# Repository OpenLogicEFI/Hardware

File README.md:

# [OpenLogicEFI](https://www.openlogicefi.com)
Formerly: DetonationEMS

</div>

OpenLogicEFI ECU's are based off an open source project called Speeduino by Josh Stewart. Currently all released boards use official Speeduino firmware. In TunerStudio set to "Board Layout" to "Speeduino 0.4"

</div>

# License
All designs are released under the [TAPR Open Hardware License v1.0](https://files.tapr.org/OHL/TAPR_Open_Hardware_License_v1.0.txt)

</div>

# Documentation

- The [Official Speeduino Manual](https://wiki.speeduino.com), documents and discord are the best places to start.

- [Official Speeduino Forum](https://speeduino.com/forum)

- [Official Speeduino Discord](https://discord.gg/jcmar3zfSJ)

- [Additional Documentation and Links](https://www.openlogicefi.com/support)

</div>

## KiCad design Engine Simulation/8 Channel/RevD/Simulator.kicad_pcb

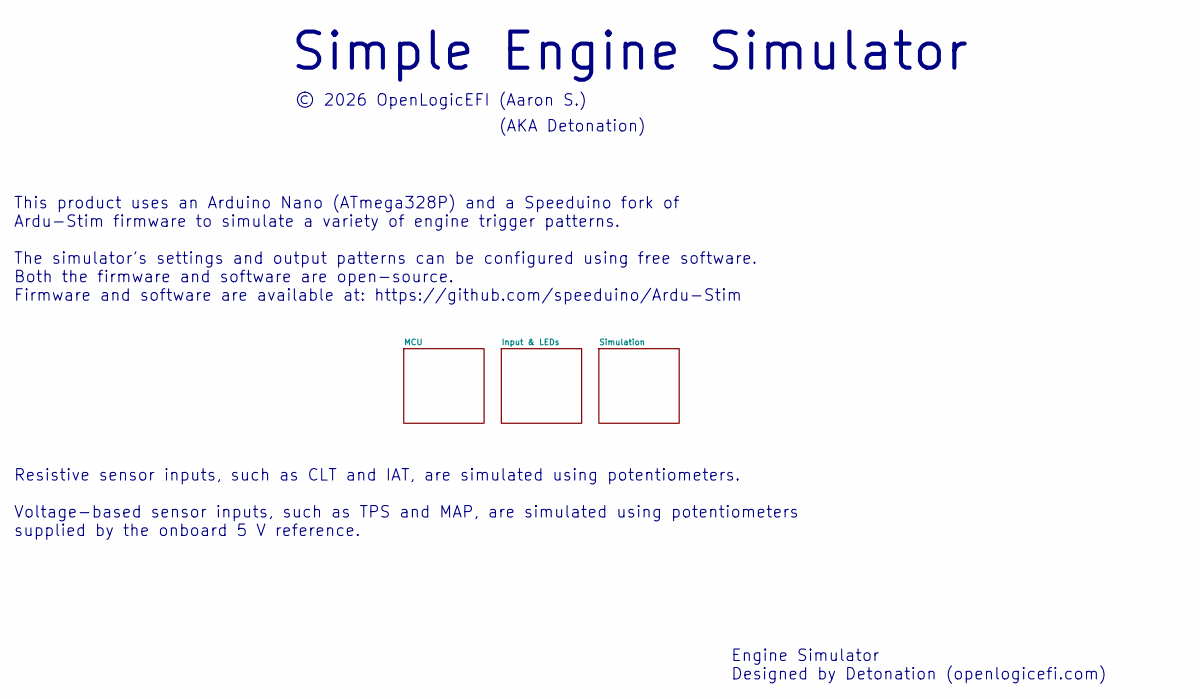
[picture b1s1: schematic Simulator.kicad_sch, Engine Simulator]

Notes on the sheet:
This product uses an Arduino Nano (ATmega328P) and a Speeduino fork of Ardu-Stim firmware to simulate a variety of engine trigger patterns. The simulator's settings and output patterns can be configured using free software. Both the firmware and software are open-source. Firmware and software are a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
Engine Simulator Designed by Detonation (openlogicefi.com)
(AKA Detonation)
Resistive sensor inputs, such as CLT and IAT, are simulated using potentiometers. Voltage-based sensor inputs, such as TPS and MAP, are simulated using potentiometers supplied by the onboard 5 V reference.
© 2026 OpenLogicEFI (Aaron S.)
Simple Engine Simulator

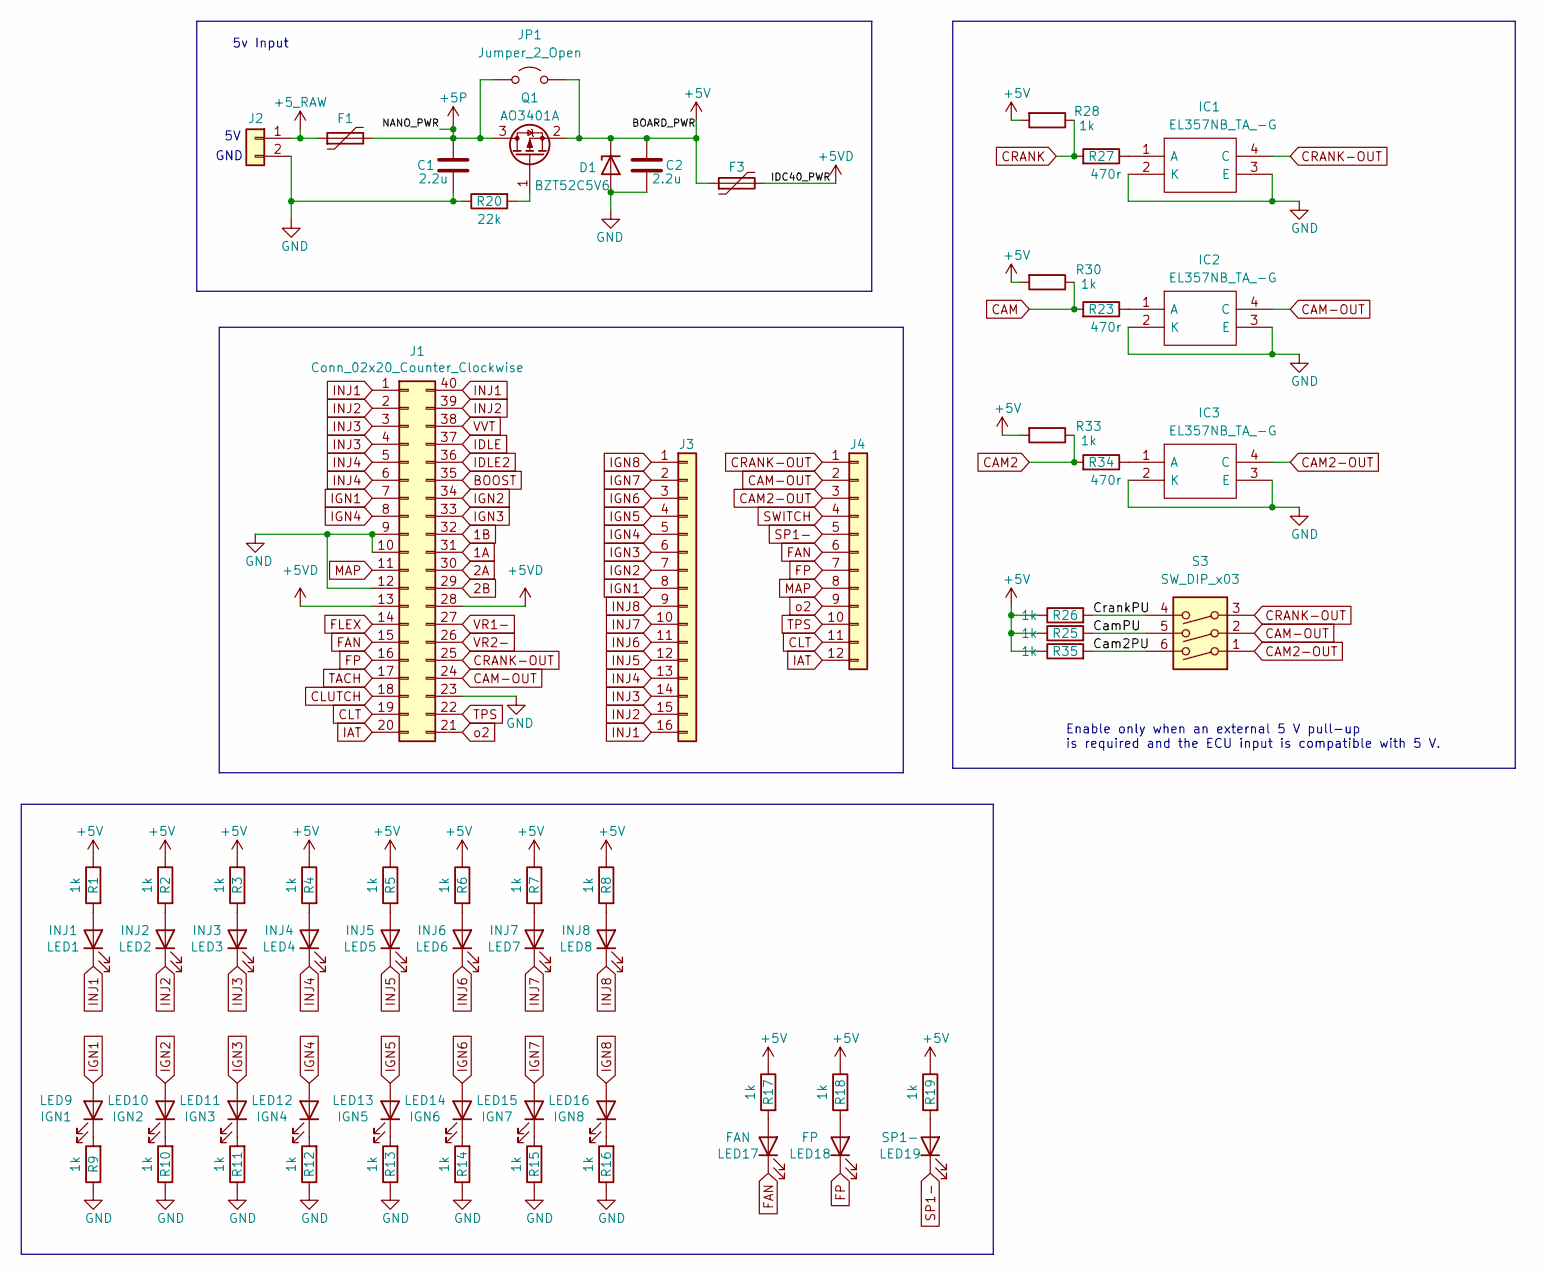
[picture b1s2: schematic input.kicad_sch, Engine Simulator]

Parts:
C1, C2: 2.2u; C_1206_3216Metric; LCSC C50254
D1: BZT52C5V6; D_SOD-123; LCSC C19077402
F1, F3: 1206L100/24NR; Fuse_1206_3216Metric; LCSC C7542957
IC1, IC2, IC3: EL357NB_TA_-G; SOP-4_3.8x4.1mm_P2.54mm; Manufacturer_Part_Number EL357NB(TA)-G; Mouser Part Number 638-EL357NBTAG
J1: Conn_02x20_Counter_Clockwise; IDC-Header_2x20_P2.54mm_Vertical_Speeduino
J2: Conn_01x04; TerminalBlock_Phoenix_PT-1,5-2-5.0-H_1x02_P5.00mm_Horizontal
J3: Conn_01x08; TerminalBlock_Phoenix_PT-1,5-16-3.5-H_1x16_P3.50mm_Horizont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
J4: Conn_01x10; TerminalBlock_Phoenix_PT-1,5-12-3.5-H_1x12_P3.50mm_Horizont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
JP1: Jumper_2_Open; SolderJumper-2_P1.3mm_Open_Rounded_NOCOURTYARD
LED1: INJ1; LED_0603_1608Metric; LCSC C2286
LED2: INJ2; LED_0603_1608Metric; LCSC C2286
LED3: INJ3; LED_0603_1608Metric; LCSC C2286
LED4: INJ4; LED_0603_1608Metric; LCSC C2286
LED5: INJ5; LED_0603_1608Metric; LCSC C2286
LED6: INJ6; LED_0603_1608Metric; LCSC C2286
LED7: INJ7; LED_0603_1608Metric; LCSC C2286
LED8: INJ8; LED_0603_1608Metric; LCSC C2286
LED9: IGN1; LED_0603_1608Metric; LCSC C2286
LED10: IGN2; LED_0603_1608Metric; LCSC C2286
LED11: IGN3; LED_0603_1608Metric; LCSC C2286
LED12: IGN4; LED_0603_1608Metric; LCSC C2286
LED13: IGN5; LED_0603_1608Metric; LCSC C2286
LED14: IGN6; LED_0603_1608Metric; LCSC C2286
LED15: IGN7; LED_0603_1608Metric; LCSC C2286
LED16: IGN8; LED_0603_1608Metric; LCSC C2286
LED17: FAN; LED_0603_1608Metric; LCSC C2286
LED18: FP; LED_0603_1608Metric; LCSC C2286
LED19: SP1-; LED_0603_1608Metric; LCSC C2286
Q1: AO3401A; SOT-23
R1, R2, R3, R4, R5, R6, R7, R8, R9, R10, R11, R12, R13, R14, R15, R16, R17, R18, R19, R25, R26, R28, R30, R33, R35: 1k; R_0603_1608Metric; LCSC C21190
R20: 22k; R_0805_2012Metric; LCSC C17560
R23, R27, R34: 470r; R_0603_1608Metric; LCSC C23179
S3: SW_DIP_x03; SW_DIP_SPSTx03_Slide_9.78x9.8mm_W7.62mm_P2.54mm

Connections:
1A: J1.31
1B: J1.32
2A: J1.30
2B: J1.29
+5P: C1.1, F1.2, JP1.1 (A), Q1.3 (D); also elsewhere on the board
+5V: C2.1, D1.1 (K), F3.1, JP1.2 (B), Q1.2 (S), R1.1, R2.1, R3.1, R4.1, R5.1, R6.1, R7.1, R8.1, R17.1, R18.1, R19.1, R25.1, R26.1, R28.2, R30.2, R33.2, R35.1; also elsewhere on the board
+5VD: F3.2, J1.13, J1.28
+5_RAW: F1.1, J2.1
/Input & LED's/Cam2PU: R35.2, S3.6
/Input & LED's/CamPU: R25.2, S3.5
/Input & LED's/CrankPU: R26.2, S3.4
BOOST: J1.35
CAM: R23.2, R30.1; also elsewhere on the board
CAM2: R33.1, R34.2; also elsewhere on the board
CAM2-OUT: IC3.4 (C), J4.3, S3.1
CAM-OUT: IC2.4 (C), J1.24, J4.2, S3.2
CLT: J1.19, J4.11; also elsewhere on the board
CLUTCH: J1.18
CRANK: R27.2, R28.1; also elsewhere on the board
CRANK-OUT: IC1.4 (C), J1.25, J4.1, S3.3
FAN: J1.15, J4.6, LED17.1 (K)
FLEX: J1.14
FP: J1.16, J4.7, LED18.1 (K)
GND: C1.2, C2.2, D1.2 (A), IC1.2 (K), IC1.3 (E), IC2.2 (K), IC2.3 (E), IC3.2 (K), IC3.3 (E), J1.9, J1.10, J1.12, J1.23, J2.2, R9.1, R10.1, R11.1, R12.1, R13.1, R14.1, R15.1, R16.1, R20.1; also elsewhere on the board
IAT: J1.20, J4.12; also elsewhere on the board
IDLE: J1.37
IDLE2: J1.36
IGN1: J1.7, J3.8, LED9.2 (A)
IGN2: J1.34, J3.7, LED10.2 (A)
IGN3: J1.33, J3.6, LED11.2 (A)
IGN4: J1.8, J3.5, LED12.2 (A)
IGN5: J3.4, LED13.2 (A)
IGN6: J3.3, LED14.2 (A)
IGN7: J3.2, LED15.2 (A)
IGN8: J3.1, LED16.2 (A)
INJ1: J1.1, J1.40, J3.16, LED1.1 (K)
INJ2: J1.2, J1.39, J3.15, LED2.1 (K)
INJ3: J1.3, J1.4, J3.14, LED3.1 (K)
INJ4: J1.5, J1.6, J3.13, LED4.1 (K)
INJ5: J3.12, LED5.1 (K)
INJ6: J3.11, LED6.1 (K)
INJ7: J3.10, LED7.1 (K)
INJ8: J3.9, LED8.1 (K)
MAP: J1.11, J4.8; also elsewhere on the board
unnamed: IC1.1 (A), R27.1
unnamed: IC2.1 (A), R23.1
unnamed: IC3.1 (A), R34.1
unnamed: LED1.2 (A), R1.2
unnamed: LED2.2 (A), R2.2
unnamed: LED3.2 (A), R3.2
unnamed: LED4.2 (A), R4.2
unnamed: LED5.2 (A), R5.2
unnamed: LED6.2 (A), R6.2
unnamed: LED7.2 (A), R7.2
unnamed: LED8.2 (A), R8.2
unnamed: LED9.1 (K), R9.2
unnamed: LED10.1 (K), R10.2
unnamed: LED11.1 (K), R11.2
unnamed: LED12.1 (K), R12.2
unnamed: LED13.1 (K), R13.2
unnamed: LED14.1 (K), R14.2
unnamed: LED15.1 (K), R15.2
unnamed: LED16.1 (K), R16.2
unnamed: LED17.2 (A), R17.2
unnamed: LED18.2 (A), R18.2
unnamed: LED19.2 (A), R19.2
unnamed: Q1.1 (G), R20.2
SP1-: J4.5, LED19.1 (K)
SWITCH: J4.4; also elsewhere on the board
TACH: J1.17
TPS: J1.22, J4.10; also elsewhere on the board
VR1-: J1.27
VR2-: J1.26
VVT: J1.38
o2: J1.21, J4.9; also elsewhere on the board

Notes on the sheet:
Enable only when an external 5 V pull-up is required and the ECU input is compatible with 5 V.
GND
5v Input

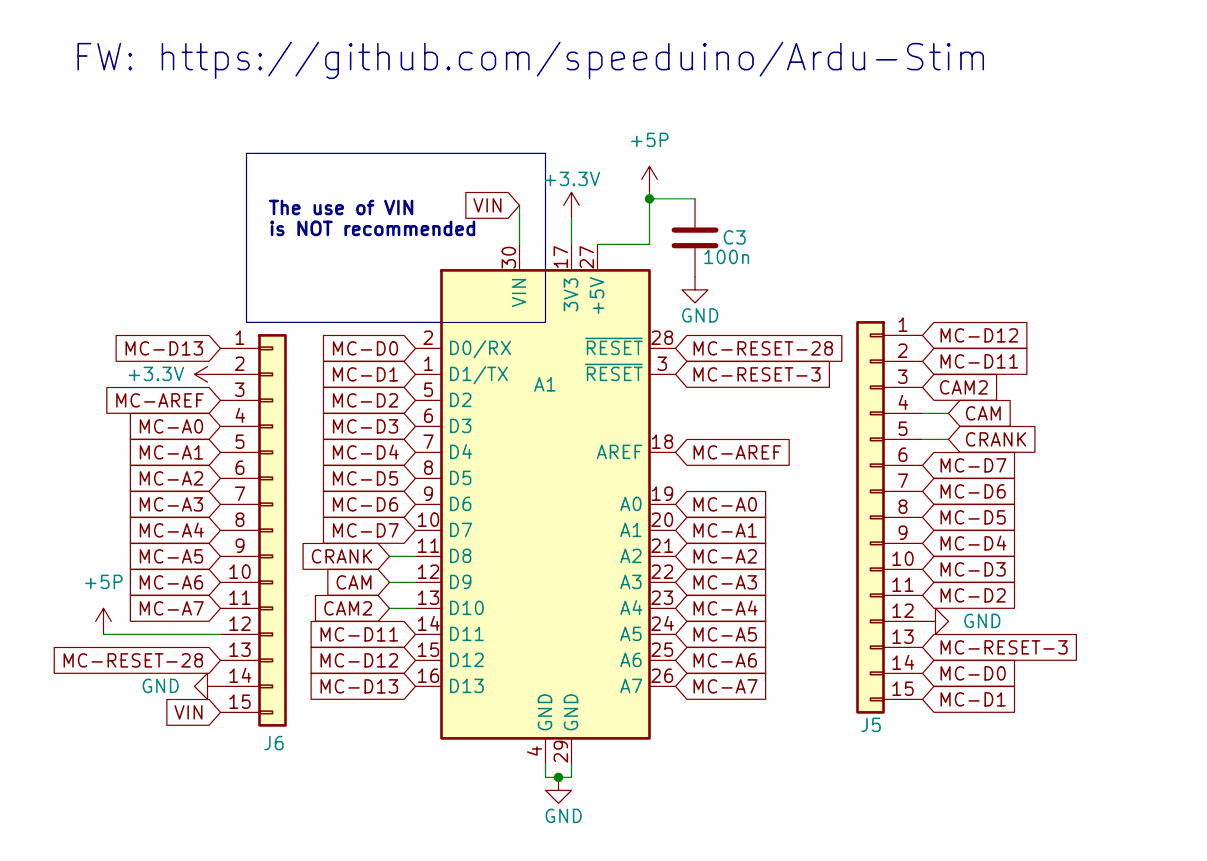
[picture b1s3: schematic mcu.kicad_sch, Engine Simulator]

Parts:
A1: Arduino_Nano_v3.x; Arduino_Nano
C3: 100n; C_0805_2012Metric; LCSC C49678
J5, J6: Conn_01x04; PinSocket_1x15_P2.54mm_Vertical

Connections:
+3.3V: A1.17 (3V3), J6.2
+5P: A1.27 (+5V), C3.1, J6.12; also elsewhere on the board
CAM: A1.12 (D9), J5.4; also elsewhere on the board
CAM2: A1.13 (D10), J5.3; also elsewhere on the board
CRANK: A1.11 (D8), J5.5; also elsewhere on the board
GND: A1.4 (GND), A1.29 (GND), C3.2, J5.12, J6.14; also elsewhere on the board
MC-A0: A1.19 (A0), J6.4; also elsewhere on the board
MC-A1: A1.20 (A1), J6.5
MC-A2: A1.21 (A2), J6.6
MC-A3: A1.22 (A3), J6.7
MC-A4: A1.23 (A4), J6.8
MC-A5: A1.24 (A5), J6.9
MC-A6: A1.25 (A6), J6.10
MC-A7: A1.26 (A7), J6.11
MC-AREF: A1.18 (AREF), J6.3
MC-D0: A1.2 (D0/RX), J5.14
MC-D1: A1.1 (D1/TX), J5.15
MC-D2: A1.5 (D2), J5.11
MC-D3: A1.6 (D3), J5.10
MC-D4: A1.7 (D4), J5.9
MC-D5: A1.8 (D5), J5.8
MC-D6: A1.9 (D6), J5.7
MC-D7: A1.10 (D7), J5.6
MC-D11: A1.14 (D11), J5.2
MC-D12: A1.15 (D12), J5.1
MC-D13: A1.16 (D13), J6.1
MC-RESET-3: A1.3 (~RESET), J5.13
MC-RESET-28: A1.28 (~RESET), J6.13
VIN: A1.30 (VIN), J6.15

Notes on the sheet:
FW: https://github.com/speeduino/Ardu-Stim
The use of VIN is NOT recommended

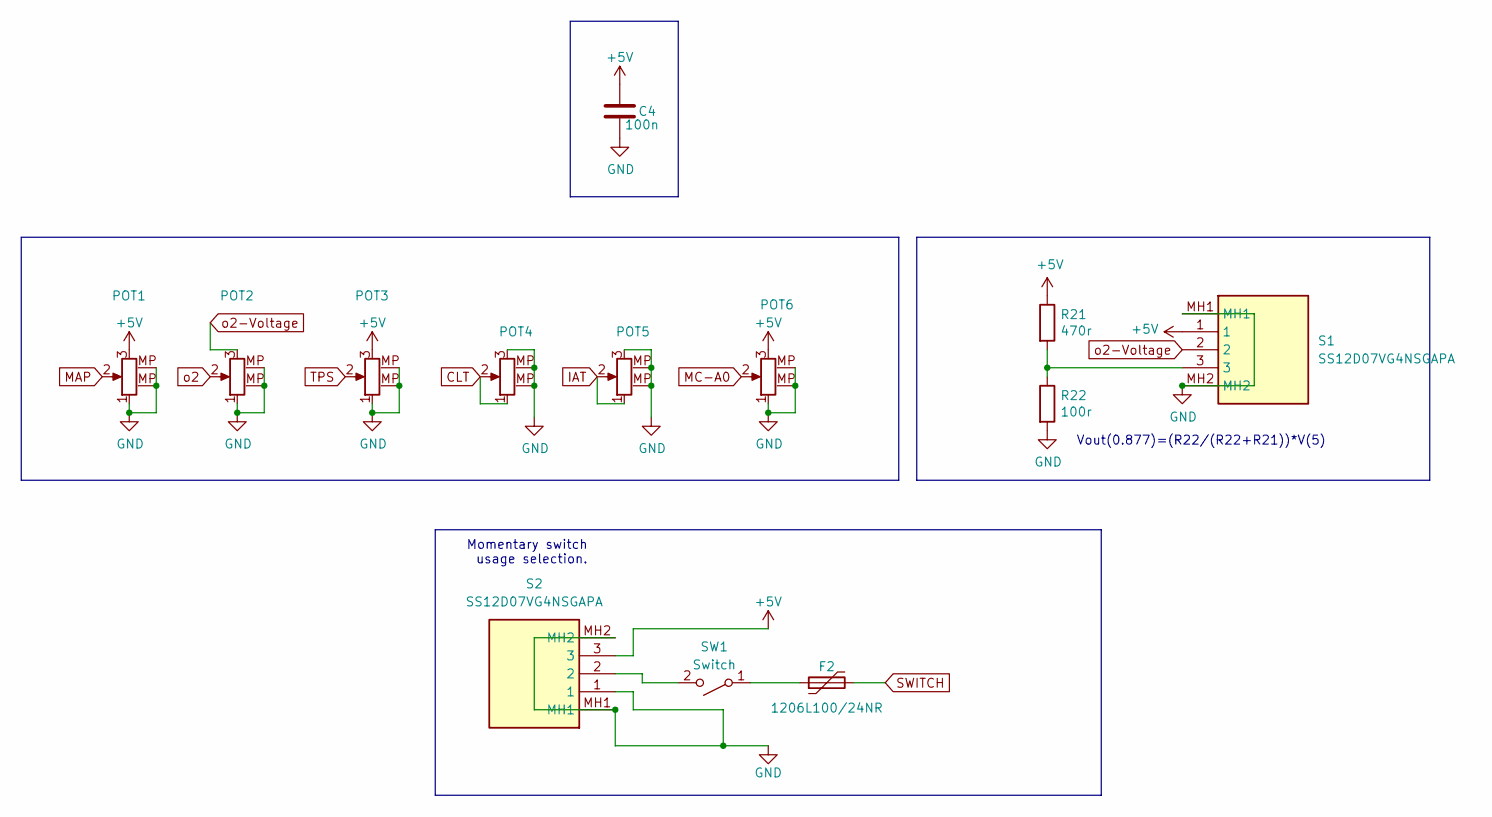
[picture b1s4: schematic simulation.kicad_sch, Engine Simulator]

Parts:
C4: 100n; C_0805_2012Metric; LCSC C49678
F2: 1206L100/24NR; Fuse_1206_3216Metric; LCSC C7542957
POT1: IAT; Potentiometer_Alps_RK09K_Single_Vertical; LCSC C202373
POT2: CLT; Potentiometer_Alps_RK09K_Single_Vertical; LCSC C202373
POT3: MAP/SP1; Potentiometer_Alps_RK09K_Single_Vertical; LCSC C202373
POT4: TPS; Potentiometer_Alps_RK09K_Single_Vertical; LCSC C202373
POT5: o2; Potentiometer_Alps_RK09K_Single_Vertical; LCSC C202373
POT6: RPM; Potentiometer_Alps_RK09K_Single_Vertical; LCSC C202373
R21: 470r; R_0603_1608Metric; LCSC C23179
R22: 100r; R_0603_1608Metric; LCSC C22775
S1, S2: SS12D07VG4NSGAPA; Manufacturer_Part_Number SS12D07VG4NSGAPA; Mouser Part Number N/A
SW1: Switch; SW_PUSH_6mm_H9.5mm

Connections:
+5V: C4.1, POT1.3, POT3.3, POT6.3, R21.1, S1.1, S2.3; also elsewhere on the board
CLT: POT4.1, POT4.2; also elsewhere on the board
GND: C4.2, POT1.1, POT1.MP (Mounting_Tap), POT2.1, POT2.MP (Mounting_Tap), POT3.1, POT3.MP (Mounting_Tap), POT4.3, POT4.MP (Mounting_Tap), POT5.3, POT5.MP (Mounting_Tap), POT6.1, POT6.MP (Mounting_Tap), R22.2, S1.MH1, S1.MH2, S2.1, S2.MH1, S2.MH2; also elsewhere on the board
IAT: POT5.1, POT5.2; also elsewhere on the board
MAP: POT1.2; also elsewhere on the board
MC-A0: POT6.2; also elsewhere on the board
unnamed: R21.2, R22.1, S1.3
unnamed: F2.1, SW1.1 (A)
unnamed: S2.2, SW1.2 (B)
SWITCH: F2.2; also elsewhere on the board
TPS: POT3.2; also elsewhere on the board
o2: POT2.2; also elsewhere on the board
o2-Voltage: POT2.3, S1.2

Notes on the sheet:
Vout(0.877)=(R22/(R22+R21))*V(5)
Momentary switch usage selection.

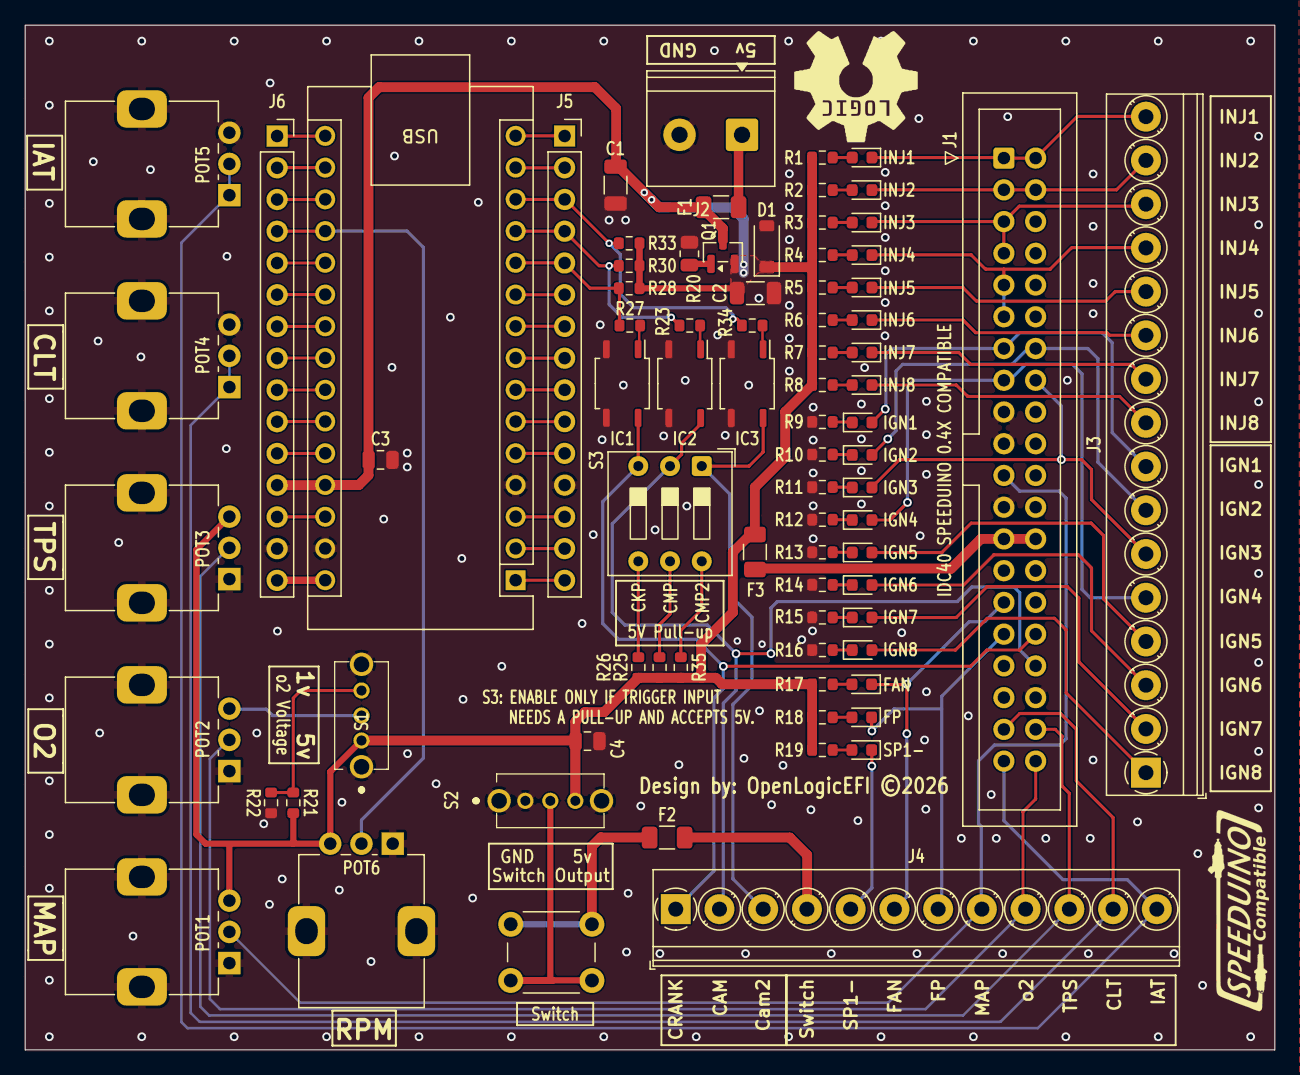
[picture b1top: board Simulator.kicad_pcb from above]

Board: 2 copper layers, 100.0 x 82.0 mm, 81 parts (1 on the bottom side), 90 nets.

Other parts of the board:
G2: Logo_Open_Hardware_Small; SpeeduinoCompatible-17mm

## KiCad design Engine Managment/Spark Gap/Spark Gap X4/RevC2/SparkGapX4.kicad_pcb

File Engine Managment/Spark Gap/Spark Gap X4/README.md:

# Spark Gap

Spark Gap x4 is an open-source, universal standalone engine management system designed
for the budget-minded enthusiast seeking a comprehensive all-in-one solution.
It is compact and feature-rich, utilizing an off-the-shelf case and connector.

Board Selection in tuner studio for this ECU is "Speeduino v0.4"

RevA: Initial Release 2024

RevB: Never released

RevC: Released 2025

RevC2: Released 2026

www.OpenLogicEFI.com

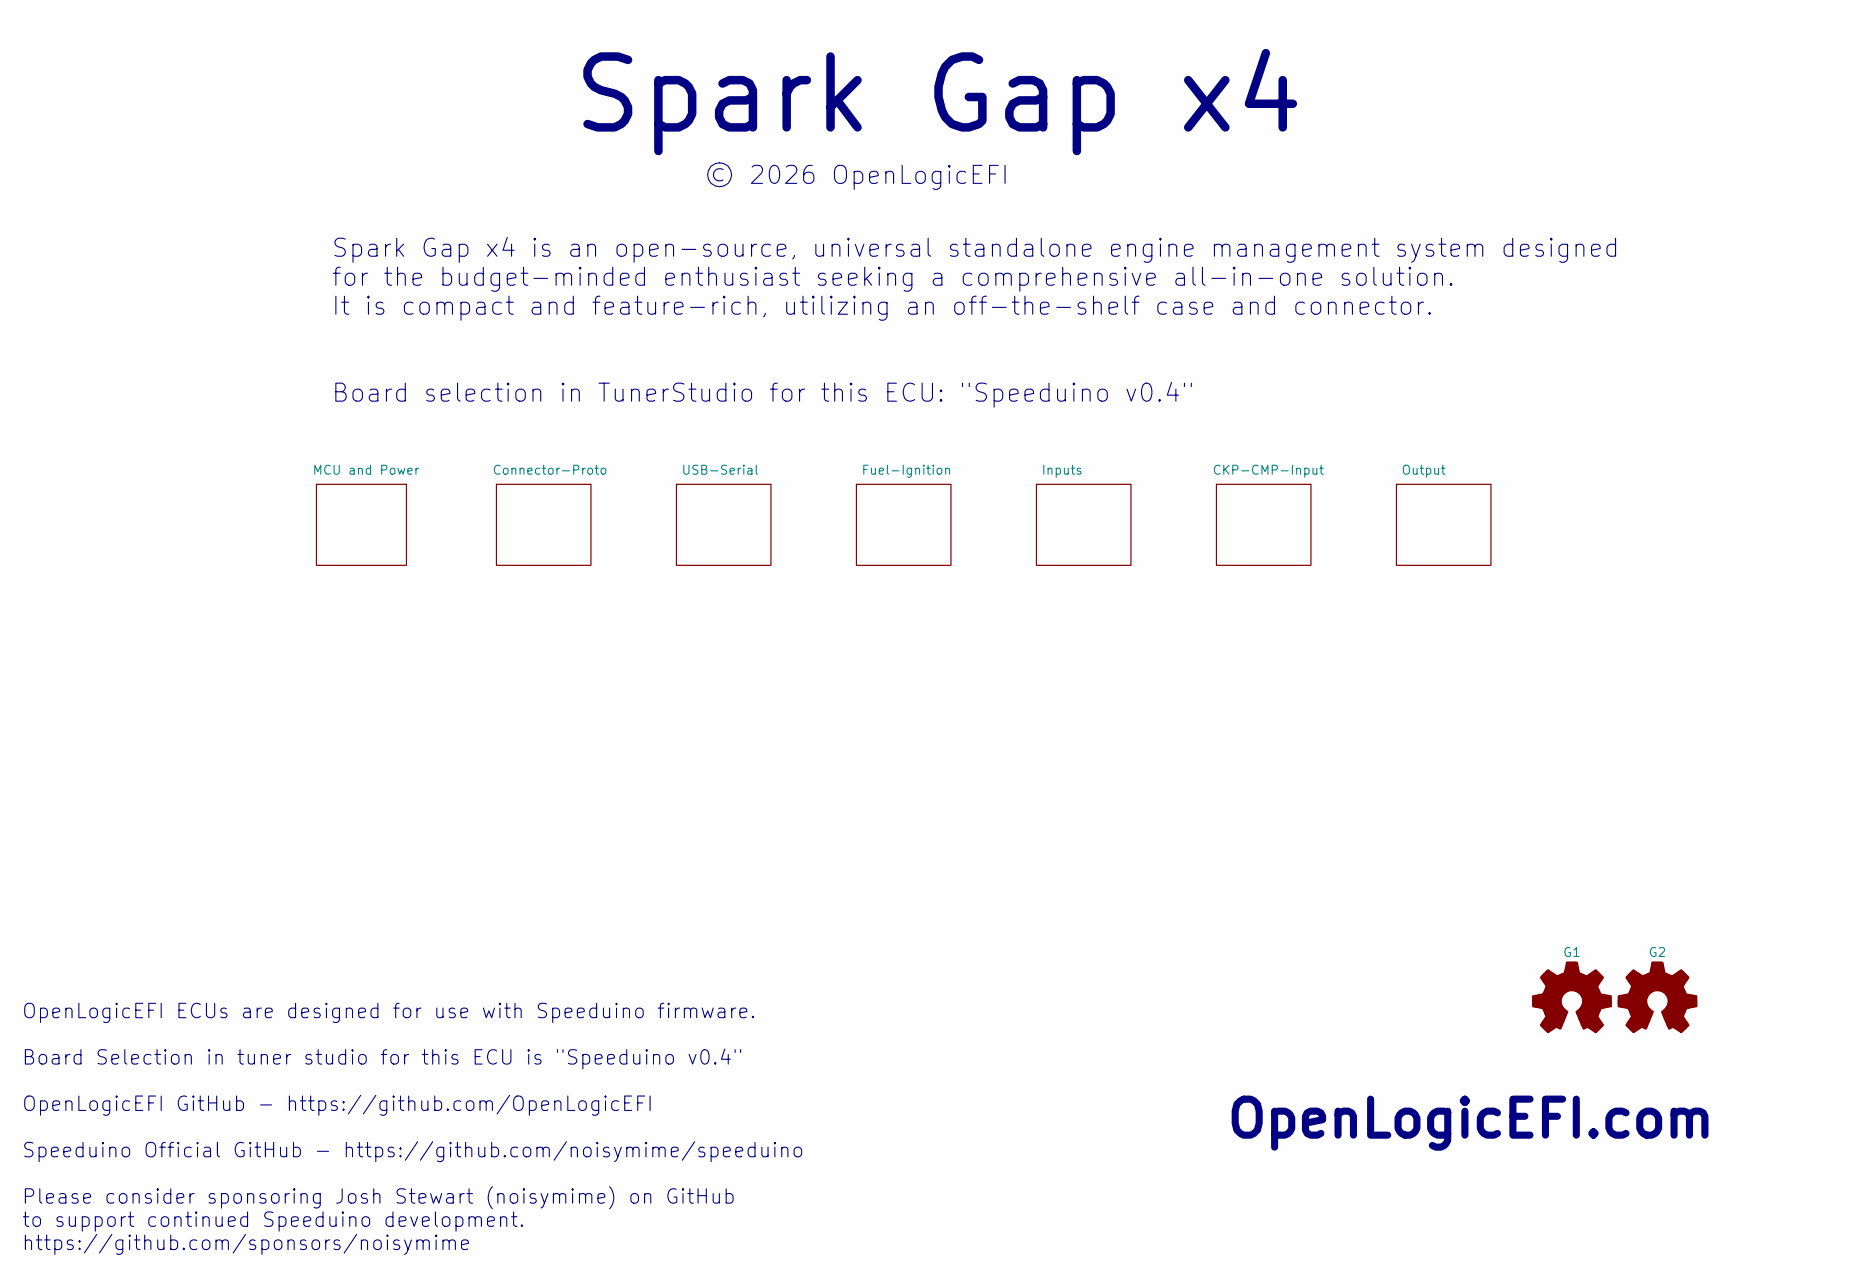
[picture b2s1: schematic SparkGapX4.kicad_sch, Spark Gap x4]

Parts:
G1: Logo_Open_Hardware_Small; SpeeduinoCompatible-14mm
G2: Logo_Open_Hardware_Small; OSHW-Logo2_7.3x6mm_SilkScreen

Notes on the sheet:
OpenLogicEFI ECUs are designed for use with Speeduino firmware. Board Selection in tuner studio for this ECU is "Speeduino v0.4" OpenLogicEFI GitHub - https://github.com/OpenLogicEFI Speeduino Official GitHub - https://github.com/noisymime/speeduino Please consider sponsoring Josh Stewart (noisymim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
© 2026 OpenLogicEFI
OpenLogicEFI.com
Spark Gap x4 is an open-source, universal standalone engine management system designed for the budget-minded enthusiast seeking a comprehensive all-in-one solution. It is compact and feature-rich, utilizing an off-the-shelf case and connector. Board selection in TunerStudio for this ECU: "Speeduino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
Spark Gap x4

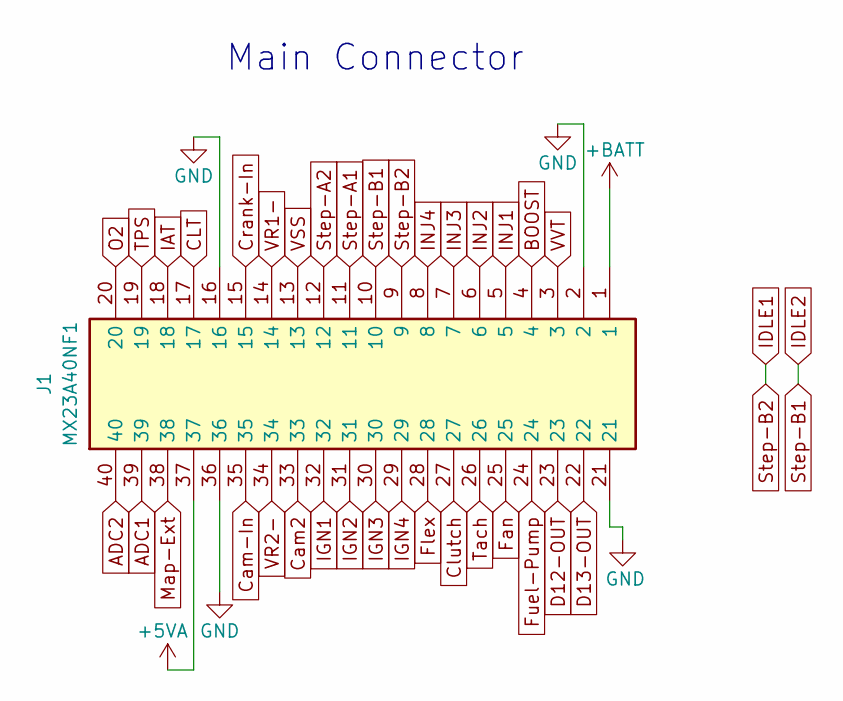
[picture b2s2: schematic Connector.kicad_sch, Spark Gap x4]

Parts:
J1: MX23A40NF1; Manufacture Part Number MX23A40NF1

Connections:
+5V: J1.37; also elsewhere on the board
+BATT: J1.1; also elsewhere on the board
ADC1: J1.39; also elsewhere on the board
ADC2: J1.40; also elsewhere on the board
BOOST: J1.4; also elsewhere on the board
CLT: J1.17; also elsewhere on the board
Cam2: J1.33; also elsewhere on the board
Cam-In: J1.35; also elsewhere on the board
Clutch: J1.27; also elsewhere on the board
Crank-In: J1.15; also elsewhere on the board
D12-OUT: J1.23; also elsewhere on the board
D13-OUT: J1.22; also elsewhere on the board
Fan: J1.25; also elsewhere on the board
Flex: J1.28; also elsewhere on the board
Fuel-Pump: J1.24; also elsewhere on the board
GND: J1.2, J1.16, J1.21, J1.36; also elsewhere on the board
IAT: J1.18; also elsewhere on the board
IDLE1: J1.9; also elsewhere on the board
IDLE2: J1.10; also elsewhere on the board
IGN1: J1.32; also elsewhere on the board
IGN2: J1.31; also elsewhere on the board
IGN3: J1.30; also elsewhere on the board
IGN4: J1.29; also elsewhere on the board
INJ1: J1.5; also elsewhere on the board
INJ2: J1.6; also elsewhere on the board
INJ3: J1.7; also elsewhere on the board
INJ4: J1.8; also elsewhere on the board
Map-Ext: J1.38; also elsewhere on the board
O2: J1.20; also elsewhere on the board
Step-A1: J1.11; also elsewhere on the board
Step-A2: J1.12; also elsewhere on the board
TPS: J1.19; also elsewhere on the board
Tach: J1.26; also elsewhere on the board
VR1-: J1.14; also elsewhere on the board
VR2-: J1.34; also elsewhere on the board
VSS: J1.13; also elsewhere on the board
VVT: J1.3; also elsewhere on the board

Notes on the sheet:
Main Connector

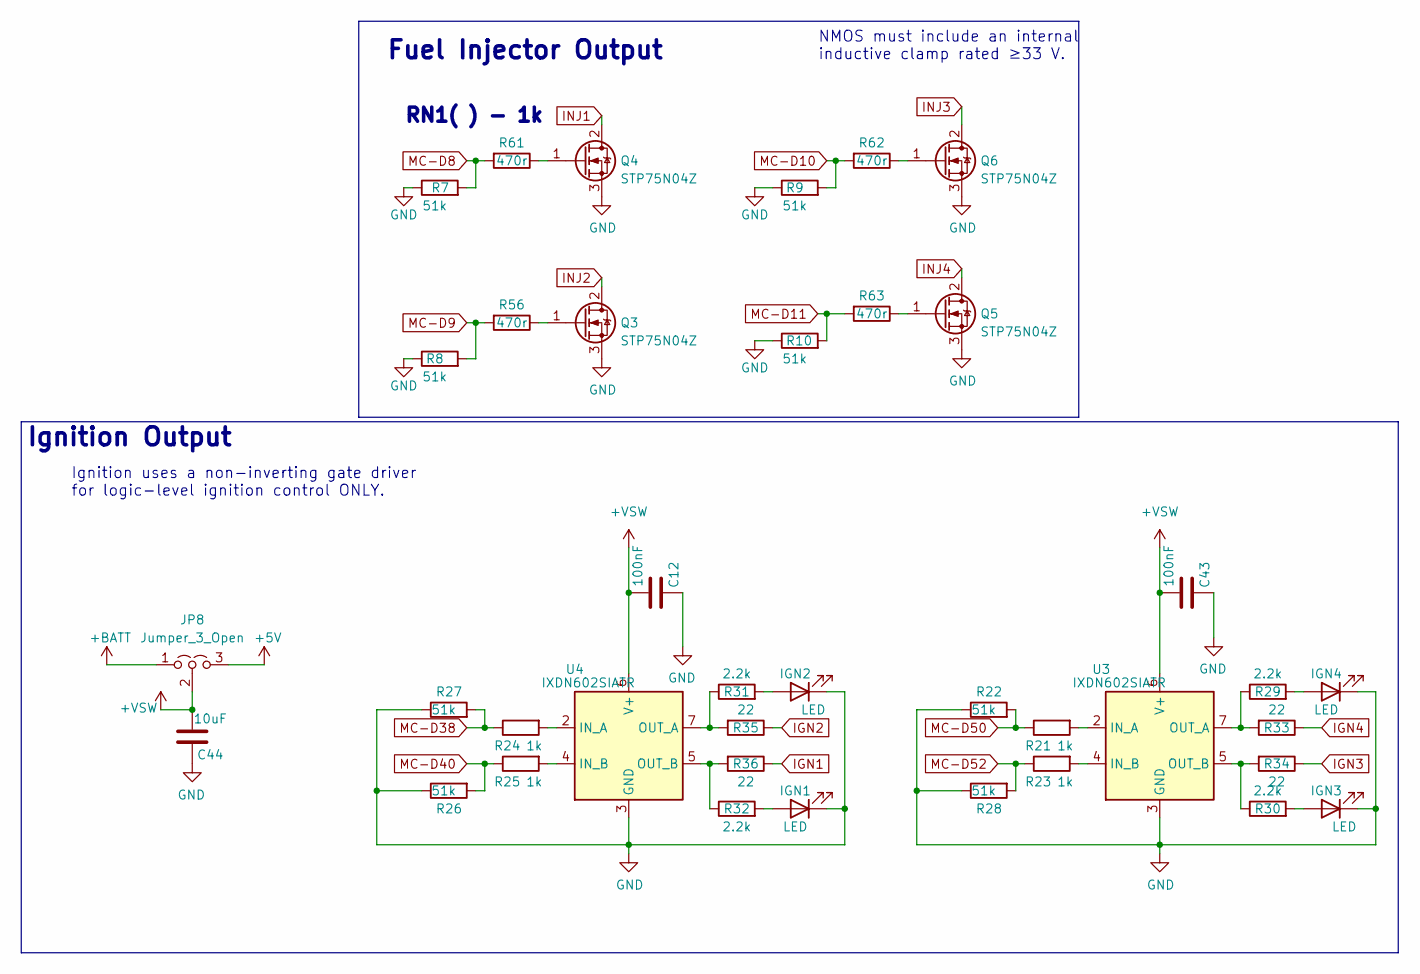
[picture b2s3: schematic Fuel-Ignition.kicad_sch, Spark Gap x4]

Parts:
C12, C43: 100nF; C_0402_1005Metric; Manufacture Part Number CL05B104KB54PNC; LCSC C307331
C44: 10uF; C_0805_2012Metric; Manufacture Part Number GRM21BR61H106KE43L; LCSC C440198
IGN1, IGN2, IGN3, IGN4: LED; LED_0603_1608Metric; Manufacture Part Number KT-0603R; LCSC C2286
JP8: Jumper_3_Open; 1x03-Proto
Q3, Q4, Q5, Q6: STP75N04Z; TO-220-3_Vertical; Manufacture Part Number STP75N04Z
R7, R8, R9, R10, R22, R26, R27, R28: 51k; R_0402_1005Metric; Manufacture Part Number 0402WGF5102TCE; LCSC C25794
R21, R23, R24, R25: 1k; R_0402_1005Metric; Manufacture Part Number 0402WGF1001TCE; LCSC C11702
R29, R30, R31, R32: 2.2k; R_0402_1005Metric; Manufacture Part Number 0402WGF2201TCE; LCSC C25879
R33, R34, R35, R36: 22; R_0805_2012Metric; Manufacture Part Number 0805W8F220JT5E; LCSC C17561
R56, R61, R62, R63: 470r; R_0402_1005Metric; Manufacture Part Number 0402WGF4700TCE; LCSC C25117
U3, U4: IXDN602SIATR; SOIC-8_3.9x4.9mm_P1.27mm; Manufacture Part Number IXDN602SIATR; LCSC C431679

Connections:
+5V: JP8.3 (B); also elsewhere on the board
+BATT: JP8.1 (A); also elsewhere on the board
+VSW: C12.1, C43.1, C44.1, JP8.2 (C), U3.6 (V+), U4.6 (V+)
GND: C12.2, C43.2, C44.2, IGN1.1 (K), IGN2.1 (K), IGN3.1 (K), IGN4.1 (K), Q3.3 (S), Q4.3 (S), Q5.3 (S), Q6.3 (S), R7.1, R8.1, R9.1, R10.1, R22.1, R26.1, R27.1, R28.1, U3.3 (GND), U4.3 (GND); also elsewhere on the board
IGN1: R36.1; also elsewhere on the board
IGN2: R35.1; also elsewhere on the board
IGN3: R34.1; also elsewhere on the board
IGN4: R33.1; also elsewhere on the board
INJ1: Q4.2 (D); also elsewhere on the board
INJ2: Q3.2 (D); also elsewhere on the board
INJ3: Q6.2 (D); also elsewhere on the board
INJ4: Q5.2 (D); also elsewhere on the board
MC-D8: R7.2, R61.2; also elsewhere on the board
MC-D9: R8.2, R56.2; also elsewhere on the board
MC-D10: R9.2, R62.2; also elsewhere on the board
MC-D11: R10.2, R63.2; also elsewhere on the board
MC-D38: R24.1, R27.2; also elsewhere on the board
MC-D40: R25.1, R26.2; also elsewhere on the board
MC-D50: R21.1, R22.2; also elsewhere on the board
MC-D52: R23.1, R28.2; also elsewhere on the board
unnamed: IGN1.2 (A), R32.2
unnamed: IGN2.2 (A), R31.2
unnamed: IGN3.2 (A), R30.2
unnamed: IGN4.2 (A), R29.2
unnamed: Q3.1 (G), R56.1
unnamed: Q4.1 (G), R61.1
unnamed: Q5.1 (G), R63.1
unnamed: Q6.1 (G), R62.1
unnamed: R21.2, U3.2 (IN_A)
unnamed: R23.2, U3.4 (IN_B)
unnamed: R29.1, R33.2, U3.7 (OUT_A)
unnamed: R30.1, R34.2, U3.5 (OUT_B)
unnamed: R24.2, U4.2 (IN_A)
unnamed: R25.2, U4.4 (IN_B)
unnamed: R31.1, R35.2, U4.7 (OUT_A)
unnamed: R32.1, R36.2, U4.5 (OUT_B)

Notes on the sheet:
Fuel Injector Output
RN1( ) - 1k
NMOS must include an internal inductive clamp rated ≥33 V.
Ignition Output
Ignition uses a non-inverting gate driver for logic-level ignition control ONLY.

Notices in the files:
Engine Managment/Pre-Ignition/Pre-Ignition x4/MX4D/Pre_Ignition.kicad_pcb:
© OpenLogicEFI 2026 (Aaron S.)
Engine Managment/Spark Gap/Spark Gap X4/RevC2/SparkGapX4.kicad_pcb:
Design by: © 2026 OpenLogicEFI
Engine Simulation/8 Channel/RevD/Simulator.kicad_pcb:
Design by: OpenLogicEFI ©2026
Modules/MAP Sensor Modules/MapDapter-4bar/map-pinned.kicad_pcb:
©OpenLogicEFI 2024
Modules/MAP Sensor Modules/MapDapter-4bar/map-pinned.kicad_sch:
© 2024 OpenLogicEFI (Aaron S.)
